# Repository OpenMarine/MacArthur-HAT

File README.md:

# MacArthur-HAT

After a few years of developing software for **OpenPlotter**, we have identified exactly what we need in terms of hardware to achieve our goals and the result is the **MacArthur HAT** (Hardware Attached on Top), an add-on board for **Raspberry Pi** running OpenPlotter. With this HAT we want to get the fully open-source boat to free ourselves from dependence on big companies and make our boats more respectful with the environment.

> __Note__
>
> KiCad files will be released when the board is in production.

> __Documentation__
>
> http://macarthur-hat-documentation.rtfd.io

> __Buy__
>
> [**OpenMarine store** (Catalonia)](https://shop.openmarine.net/home/23-macarthur-hat.html)
> 
> [**Wegmatt store** (US)](https://shop.wegmatt.com/collections/openmarine)

> __Support__
>
> https://forum.openmarine.net/forumdisplay.php?fid=29

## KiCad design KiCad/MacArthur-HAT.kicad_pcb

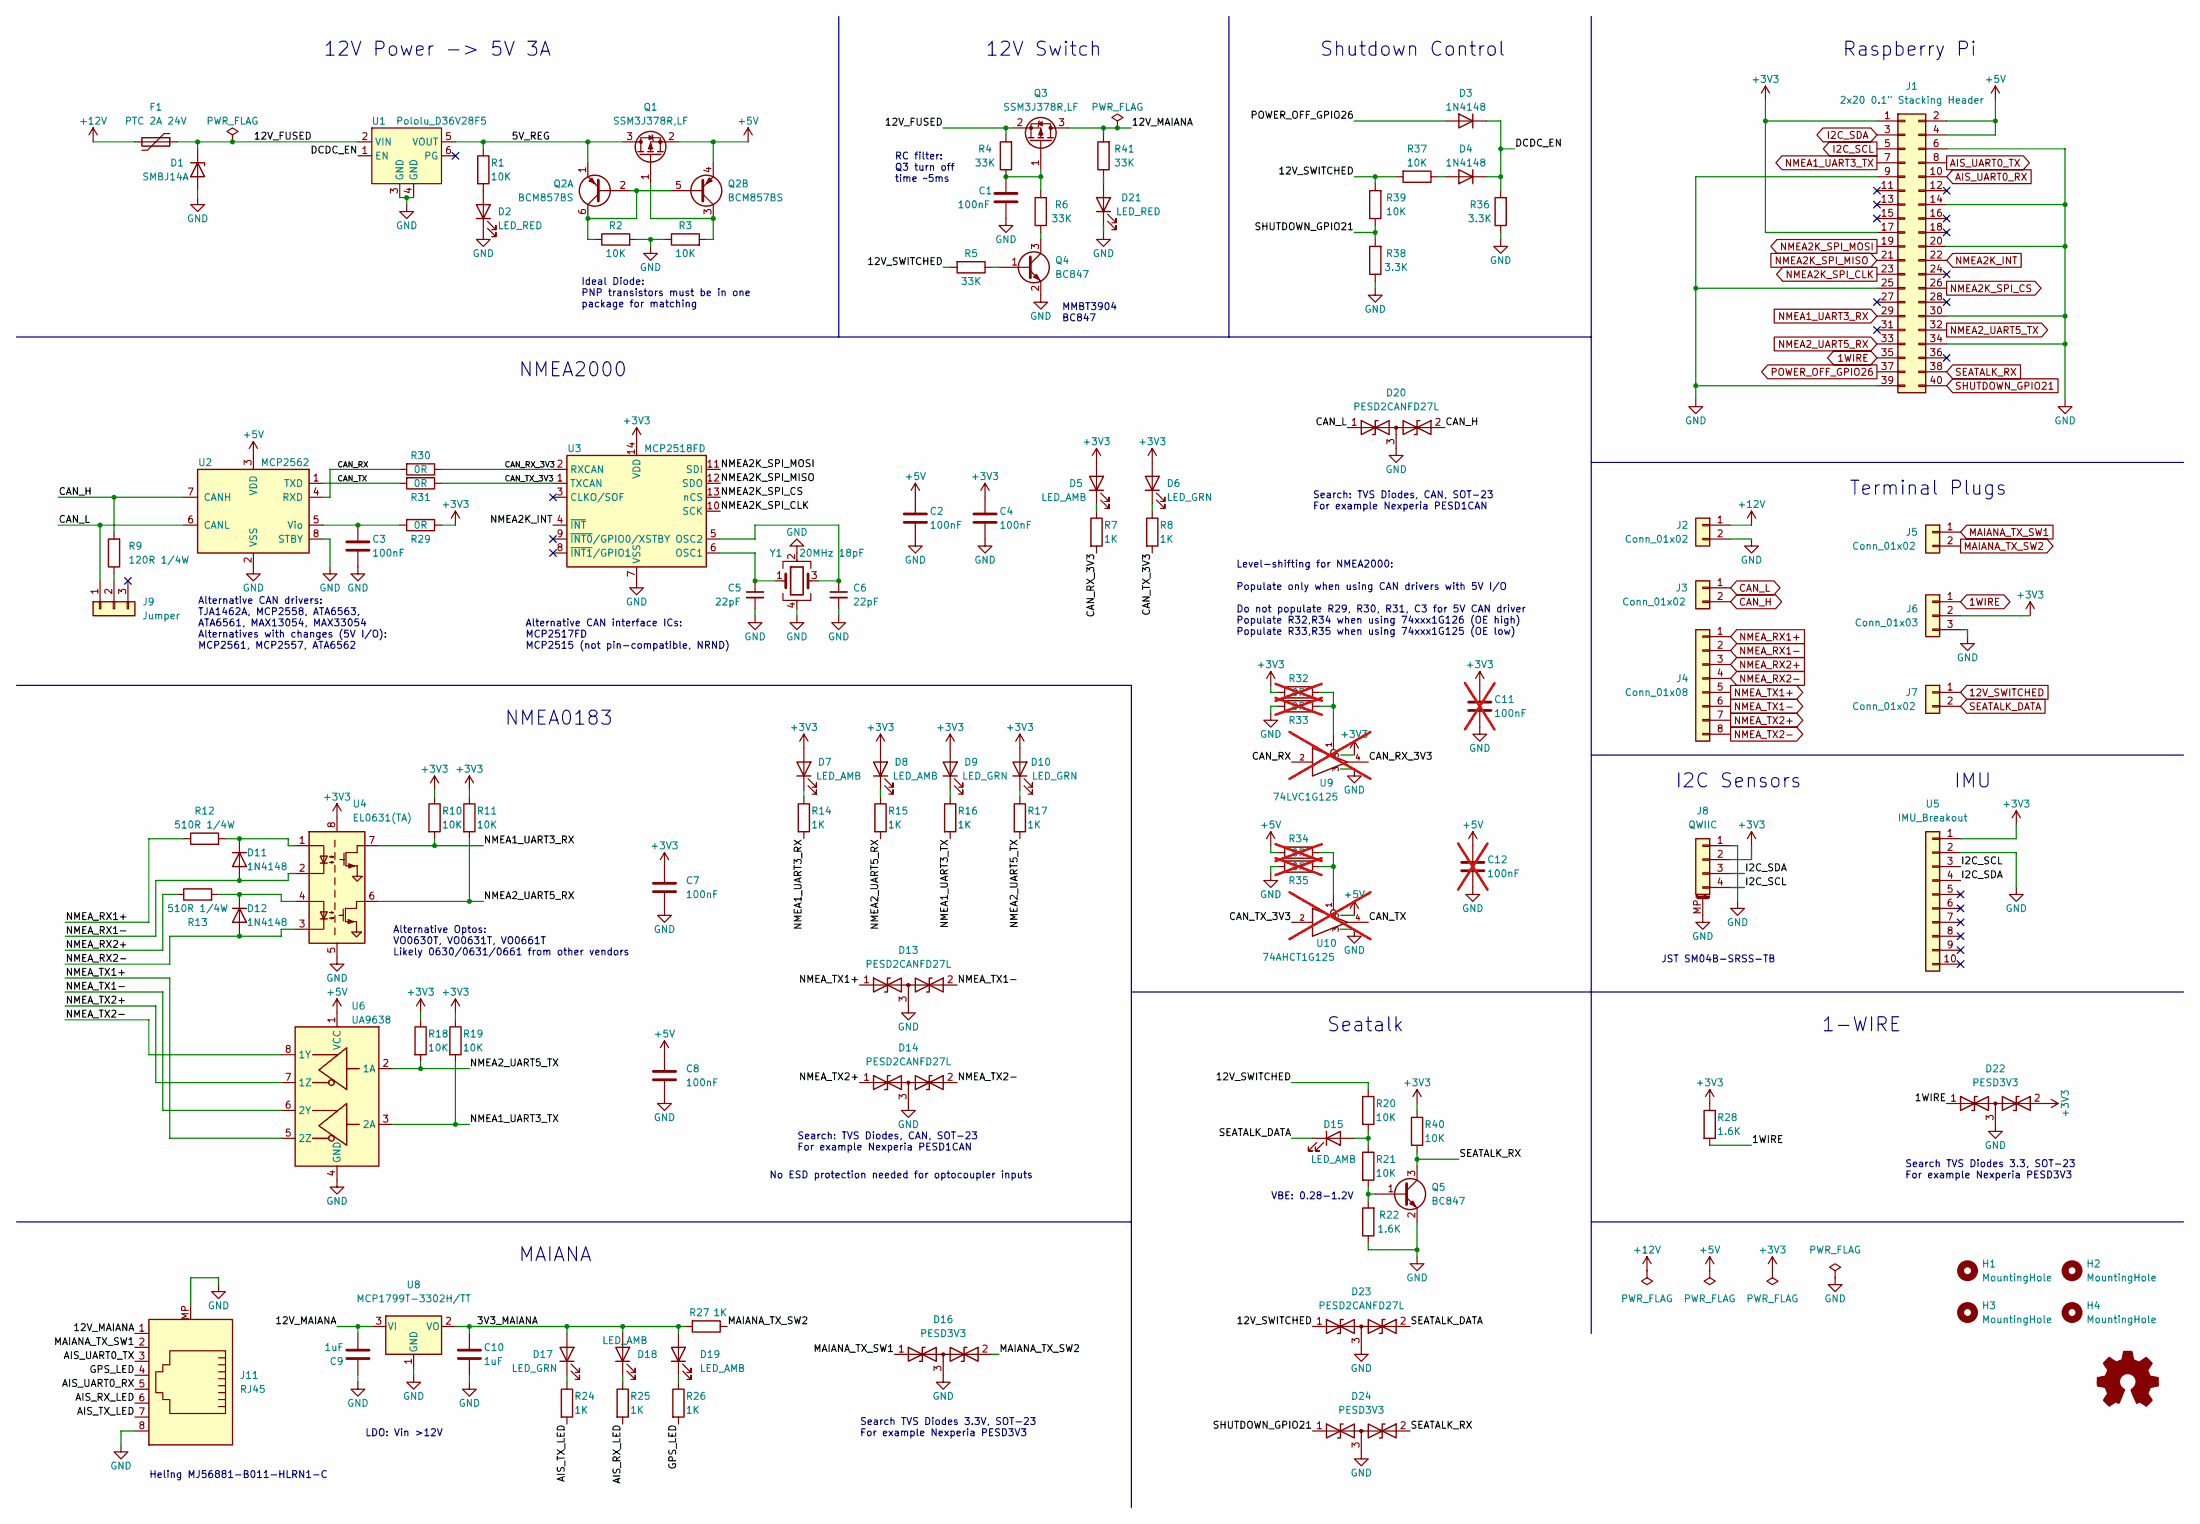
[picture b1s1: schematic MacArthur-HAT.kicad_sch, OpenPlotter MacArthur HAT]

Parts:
C1, C2, C3, C4, C7, C8: 100nF; C_0603_1608Metric
C5, C6: 22pF; C_0603_1608Metric
C9, C10: 1uF; C_0603_1608Metric
C11, C12: 100nF; C_0603_1608Metric; not fitted
D1: SMBJ14A; D_SMB; MPN SMBJ14A
D2, D21: LED_RED; LED_0603_1608Metric
D3, D4, D11, D12: 1N4148; D_SOD-323; MPN 1N4148WS
D5, D7, D8, D15, D18, D19: LED_AMB; LED_0603_1608Metric
D6, D9, D10, D17: LED_GRN; LED_0603_1608Metric
D13, D14, D20, D23: PESD2CANFD27L; SOT-23; MPN PESD2CAN
D16, D22, D24: PESD3V3; SOT-23; MPN PESD3V3S2UT,215
F1: PTC 2A 24V; Fuse_2920_7451Metric; MPN BSMD2920-200-24V
H1, H2, H3, H4: MountingHole; MountingHole_2.7mm_M2.5
J1: 2x20 0.1" Stacking Header; Raspberry_Pi_Stacking_Header
J2, J3, J5, J7: Conn_01x02; PhoenixContact_MC_1,5_2-G-3.5_1x02_P3.50mm_Horizontal
J4: Conn_01x08; PhoenixContact_MC_1,5_8-G-3.5_1x08_P3.50mm_Horizontal
J6: Conn_01x03; PhoenixContact_MC_1,5_3-G-3.5_1x03_P3.50mm_Horizontal
J8: QWIIC; JST_SH_SM04B-SRSS-TB_1x04-1MP_P1.00mm_Horizontal; MPN SM04B-SRSS-TB(LF)(SN)
J9: Jumper; PinHeader_1x03_P2.54mm_Vertical
J11: RJ45; RJ45-SMD_MJ56881-B011-HXRN1-C; MPN MJ56881-B011-HLRN1-C
LOGO1: Logo_Open_Hardware_Small; OSHW-Symbol_6.7x6mm_SilkScreen
Q1, Q3: SSM3J378R,LF; SOT-23; MPN SSM3J378R,LF
Q2: BCM857BS; SOT-363_SC-70-6; MPN BCM857BS
Q4, Q5: BC847; SOT-23; MPN BC847
R1, R2, R3, R10, R11, R18, R19, R20, R21, R37, R39, R40: 10K; R_0603_1608Metric
R4, R5, R6, R41: 33K; R_0603_1608Metric
R7, R8, R14, R15, R16, R17, R24, R25, R26, R27: 1K; R_0603_1608Metric
R9: 120R 1/4W; R_1206_3216Metric
R12, R13: 510R 1/4W; R_1206_3216Metric
R22, R28: 1.6K; R_0603_1608Metric
R29, R30, R31: 0R; R_0603_1608Metric
R32, R33, R34, R35: 0R; R_0603_1608Metric; not fitted
R36, R38: 3.3K; R_0603_1608Metric
U1: Pololu_D36V28F5; Pololu_D36V28Fx_reverse
U2: MCP2562; SOIC-8_3.9x4.9mm_P1.27mm; MPN MCP2562
U3: MCP2518FD; SOIC-14_3.9x8.7mm_P1.27mm; MPN MCP2518FD
U4: EL0631(TA); SOIC-8H_3.9x5.8mm_P1.27mm; MPN EL0631(TA)
U5: IMU_Breakout; CJMCU-96802-20948
U6: UA9638; SOIC-8_3.9x4.9mm_P1.27mm; MPN UA9638
U8: MCP1799T-3302H/TT; SOT-23; MPN MCP1799T-3302H/TT
U9: 74LVC1G125; SOT-23-5; not fitted
U10: 74AHCT1G125; SOT-23-5; not fitted
Y1: 20MHz 18pF; Crystal_SMD_3225-4Pin_3.2x2.5mm

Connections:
1WIRE: D22.1 (A1), J1.35, J6.1, R28.2
12V_SWITCHED: D23.1 (A1), J7.1, R5.2, R20.1, R37.2, R39.2
+3V3: C4.1, C7.1, C11.1, D5.2 (A), D6.2 (A), D7.2 (A), D8.2 (A), D9.2 (A), D10.2 (A), D22.2 (A2), J1.1, J1.17, J6.2, J8.2, R10.1, R11.1, R18.1, R19.1, R28.1, R29.1, R32.2, R40.1, U3.14 (VDD), U4.8 (VCC), U5.1, U9.5
+5V: C2.1, C8.1, C12.1, J1.2, J1.4, Q1.2 (S), Q2.4 (E2), R34.2, U2.3 (VDD), U6.1 (VCC), U10.5
+12V: F1.2, J2.1
/3V3_MAIANA: C10.1, D17.2 (A), D18.2 (A), D19.2 (A), R27.2, U8.2 (VO)
/5V_REG: Q1.3 (D), Q2.1 (E1), R1.1, U1.5 (VOUT)
/12V_FUSED: D1.1 (K), F1.1, Q3.2 (S), R4.2, U1.2 (VIN)
/12V_MAIANA: C9.2, J11.1, Q3.3 (D), R41.2, U8.3 (VI)
/AIS_RX_LED: J11.6, R25.2
/AIS_TX_LED: J11.7, R24.2
/CAN_RX: R30.2, U2.4 (RXD), U9.2
/CAN_RX_3V3: R7.2, R30.1, U3.2 (RXCAN), U9.4
/CAN_TX: R31.2, U2.1 (TXD), U10.4
/CAN_TX_3V3: R8.2, R31.1, U3.1 (TXCAN), U10.2
/DCDC_EN: D3.1 (K), D4.1 (K), R36.2, U1.1 (EN)
/GPS_LED: J11.4, R26.2
AIS_UART0_RX: J1.10, J11.5
AIS_UART0_TX: J1.8, J11.3
CAN_H: D20.2 (A2), J3.2, R9.2, U2.7 (CANH)
CAN_L: D20.1 (A1), J3.1, J9.1, U2.6 (CANL)
GND: C1.2, C2.2, C3.2, C4.2, C5.2, C6.2, C7.2, C8.2, C9.1, C10.2, C11.2, C12.2, D1.2 (A), D2.1 (K), D13.3 (common), D14.3 (common), D16.3 (common), D20.3 (common), D21.1 (K), D22.3 (common), D23.3 (common), D24.3 (common), J1.6, J1.9, J1.14, J1.20, J1.25, J1.30, J1.34, J1.39, J2.2, J6.3, J8.1, J8.MP (MountPin), J11.8, J11.MP, Q4.2 (E), Q5.2 (E), R2.2, R3.1, R22.1, R33.1, R35.1, R36.1, R38.1, U1.3 (GND), U1.4 (GND), U2.2 (VSS), U2.8 (STBY), U3.7 (VSS), U3.15 (VSS), U4.5 (GND), U5.2, U6.4 (GND), U8.1 (GND), U9.3, U10.3, Y1.2, Y1.4
I2C_SCL: J1.5, J8.4, U5.3
I2C_SDA: J1.3, J8.3, U5.4
MAIANA_TX_SW1: D16.1 (A1), J5.1, J11.2
MAIANA_TX_SW2: D16.2 (A2), J5.2, R27.1
NMEA1_UART3_RX: J1.29, R10.2, R14.2, U4.7 (VO1)
NMEA1_UART3_TX: J1.7, R16.2, R19.2, U6.3 (2A)
NMEA2K_INT: J1.22, U3.4 (~INT)
NMEA2K_SPI_CLK: J1.23, U3.10 (SCK)
NMEA2K_SPI_CS: J1.26, U3.13 (nCS)
NMEA2K_SPI_MISO: J1.21, U3.12 (SDO)
NMEA2K_SPI_MOSI: J1.19, U3.11 (SDI)
NMEA2_UART5_RX: J1.33, R11.2, R15.2, U4.6 (VO2)
NMEA2_UART5_TX: J1.32, R17.2, R18.2, U6.2 (1A)
NMEA_RX1+: J4.1, R12.1
NMEA_RX1-: D11.2 (A), J4.2, U4.2 (C1)
NMEA_RX2+: J4.3, R13.1
NMEA_RX2-: D12.2 (A), J4.4, U4.3 (C2)
NMEA_TX1+: D13.1 (A1), J4.5, U6.5 (2Z)
NMEA_TX1-: D13.2 (A2), J4.6, U6.6 (2Y)
NMEA_TX2+: D14.1 (A1), J4.7, U6.7 (1Z)
NMEA_TX2-: D14.2 (A2), J4.8, U6.8 (1Y)
unnamed: D2.2 (A), R1.2
unnamed: D4.2 (A), R37.1
unnamed: D5.1 (K), R7.1
unnamed: D6.1 (K), R8.1
unnamed: D7.1 (K), R14.1
unnamed: D8.1 (K), R15.1
unnamed: D9.1 (K), R16.1
unnamed: D10.1 (K), R17.1
unnamed: D11.1 (K), R12.2, U4.1 (A1)
unnamed: D12.1 (K), R13.2, U4.4 (A2)
unnamed: D15.2 (A), R20.2, R21.1
unnamed: D17.1 (K), R24.1
unnamed: D18.1 (K), R25.1
unnamed: D19.1 (K), R26.1
unnamed: D21.2 (A), R41.1
unnamed: J9.2, R9.1
unnamed: Q1.1 (G), Q2.3 (C2), R3.2
unnamed: Q2.2 (B1), Q2.5 (B2), Q2.6 (C1), R2.1
unnamed: C1.1, Q3.1 (G), R4.1, R6.2
unnamed: Q4.1 (B), R5.1
unnamed: Q4.3 (C), R6.1
unnamed: Q5.1 (B), R21.2, R22.2
unnamed: R32.1, R33.2, U9.1
unnamed: R34.1, R35.2, U10.1
unnamed: C3.1, R29.2, U2.5 (Vio)
unnamed: C5.1, U3.6 (OSC1), Y1.1
unnamed: C6.1, U3.5 (OSC2), Y1.3
POWER_OFF_GPIO26: D3.2 (A), J1.37
SEATALK_DATA: D15.1 (K), D23.2 (A2), J7.2
SEATALK_RX: D24.2 (A2), J1.38, Q5.3 (C), R40.2
SHUTDOWN_GPIO21: D24.1 (A1), J1.40, R38.2, R39.1

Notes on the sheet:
IMU
Alternative CAN interface ICs: MCP2517FD MCP2515 (not pin-compatible, NRND)
I2C Sensors
Raspberry Pi
RC filter: Q3 turn off time ~5ms
Ideal Diode: PNP transistors must be in one package for matching
JST SM04B-SRSS-TB
Alternative CAN drivers: TJA1462A, MCP2558, ATA6563, ATA6561, MAX13054, MAX33054 Alternatives with changes (5V I/O): MCP2561, MCP2557, ATA6562
Level-shifting for NMEA2000: Populate only when using CAN drivers with 5V I/O Do not populate R29, R30, R31, C3 for 5V CAN driver Populate R32,R34 when using 74xxx1G126 (OE high) Populate R33,R35 when using 74xxx1G125 (OE low)
Search TVS Diodes 3.3, SOT-23 For example Nexperia PESD3V3
MMBT3904 BC847
NMEA0183
Alternative Optos: VO0630T, VO0631T, VO0661T Likely 0630/0631/0661 from other vendors
No ESD protection needed for optocoupler inputs
Search: TVS Diodes, CAN, SOT-23 For example Nexperia PESD1CAN
1-WIRE
Heling MJ56881-B011-HLRN1-C
NMEA2000
Search TVS Diodes 3.3V, SOT-23 For example Nexperia PESD3V3
LDO: Vin >12V
VBE: 0.28-1.2V
12V Switch
Shutdown Control
12V Power -> 5V 3A
MAIANA
Terminal Plugs
Seatalk

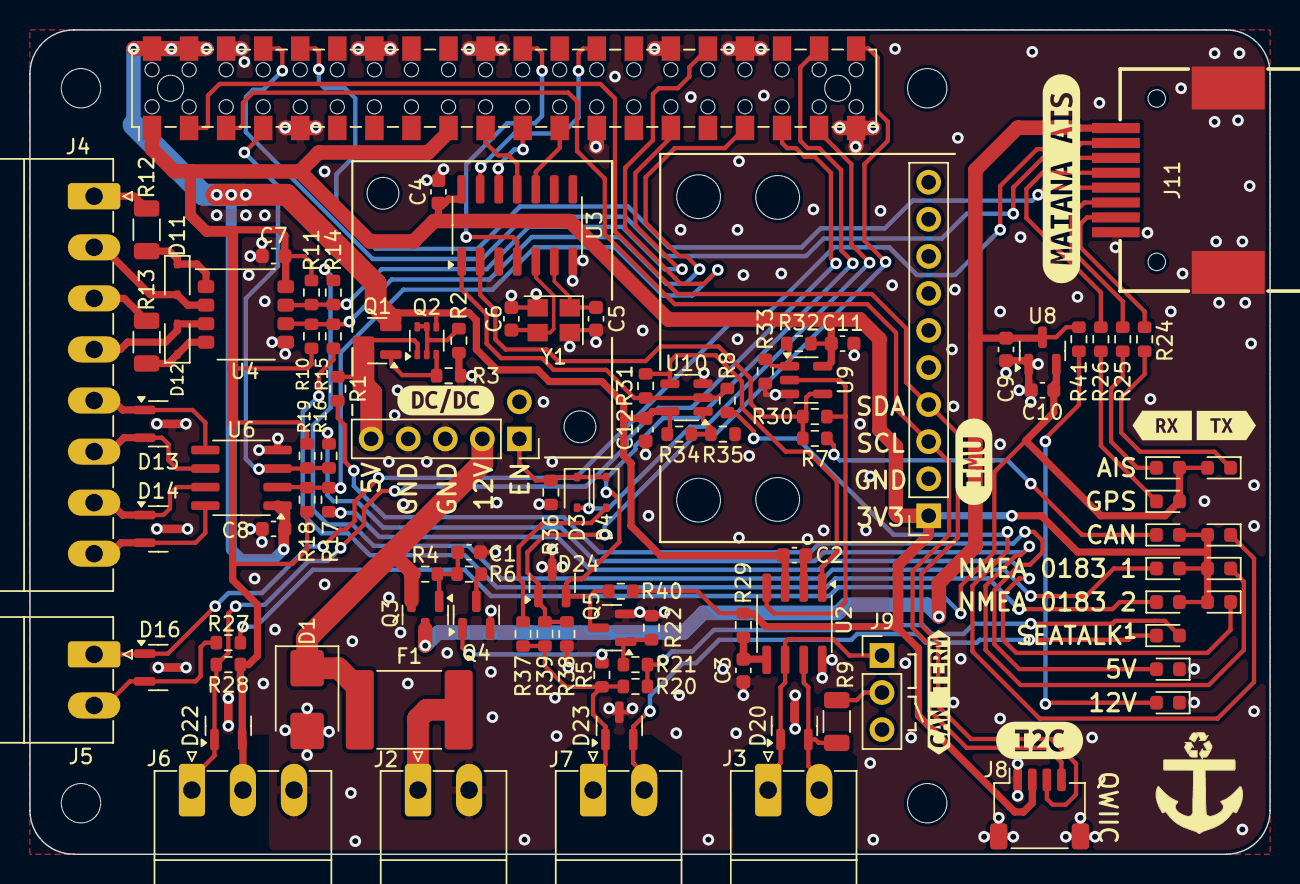
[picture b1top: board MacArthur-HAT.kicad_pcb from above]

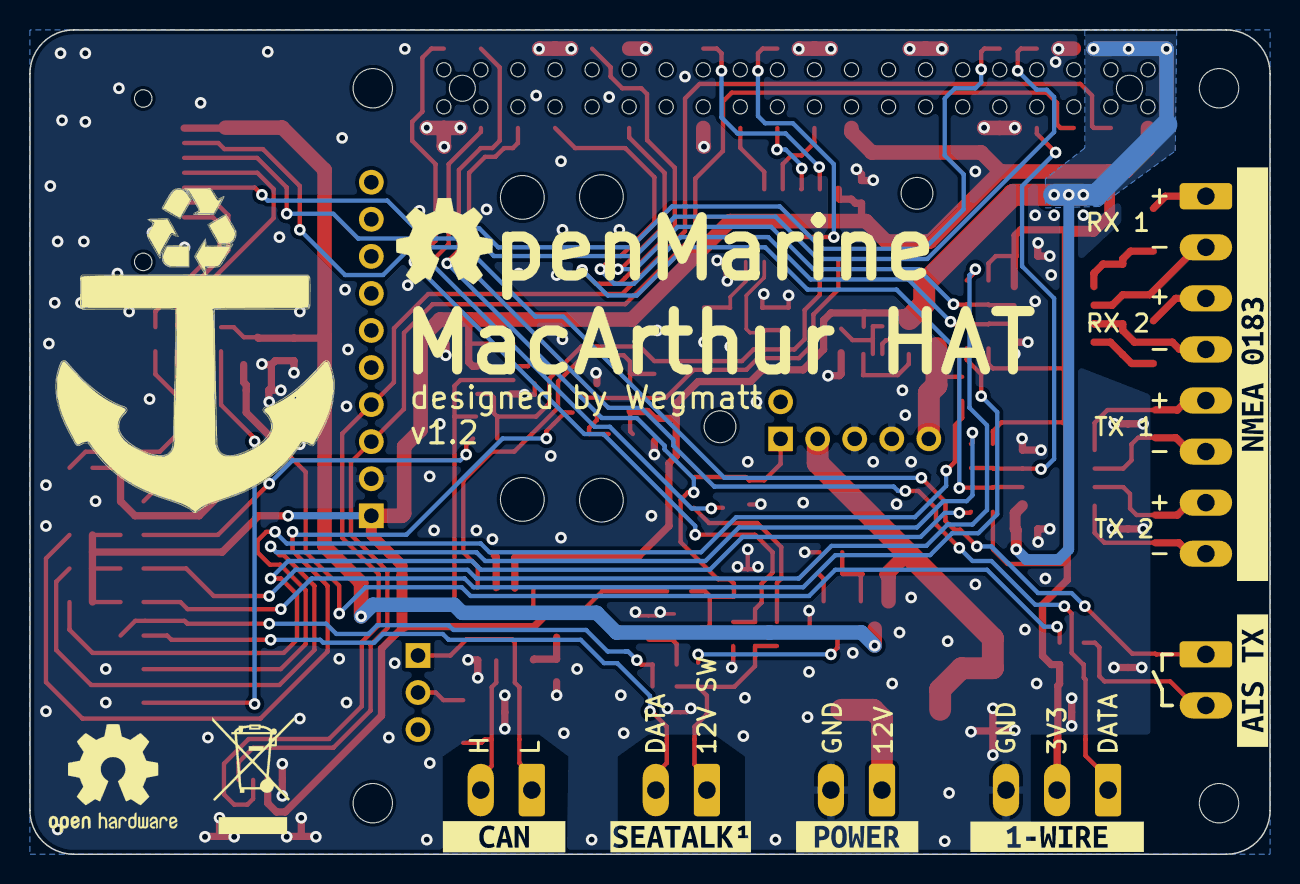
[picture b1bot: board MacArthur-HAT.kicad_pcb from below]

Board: 4 copper layers, 85.0 x 56.5 mm, 120 parts (7 on the bottom side), 74 nets.

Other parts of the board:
kibuzzard-63BC76FF: G***; kibuzzard-63BC76FF
kibuzzard-63BC7717: G***; kibuzzard-63BC7717
kibuzzard-637EF3F9: G***; kibuzzard-637EF3F9
kibuzzard-637EF437: G***; kibuzzard-637EF437
kibuzzard-637EF583: G***; kibuzzard-637EF583
kibuzzard-637EFEBF: G***; kibuzzard-637EFEBF
kibuzzard-637EFF6C: G***; kibuzzard-637EFF6C
kibuzzard-637F0005: G***; kibuzzard-637F0005
kibuzzard-637FCC15: G***; kibuzzard-637FCC15
kibuzzard-637FCC47: G***; kibuzzard-637FCC47
kibuzzard-637FCC76: G***; kibuzzard-637FCC76
kibuzzard-637FCC90: G***; kibuzzard-637FCC90
kibuzzard-646FE67F: G***; kibuzzard-646FE67F

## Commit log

2023-02-18 Create LICENCE
2023-02-18 Update LICENCE
2023-02-18 Create CHANGES
2023-03-21 change docs file names
2023-03-21 add files
2023-03-21 add links
2023-03-22 Rename LICENCE to LICENSE
2023-03-30 add forum
2023-06-15 new schematic
2023-06-15 new render
2023-06-16 new diagram
2023-06-25 new docs
2023-06-25 update changes list
2023-06-28 corrections in changes list
2023-10-29 update schematic
2023-10-29 update changes log
2023-10-31 update 3D image
2023-10-31 update diagram
2023-11-10 update docs
2023-12-06 fix table
2024-01-12 add 3D file
2024-01-12 add warning about seatalk1 and RPi 5
2024-03-14 update docs link
2024-05-09 Switch to online docs
2024-05-31 Add sources
2024-06-01 unzip kicad files

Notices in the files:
KiCad/MacArthur-HAT.kicad_pcb:
© 2023-2024 OpenMarine & Wegmatt
License: CERN-OHL-S
